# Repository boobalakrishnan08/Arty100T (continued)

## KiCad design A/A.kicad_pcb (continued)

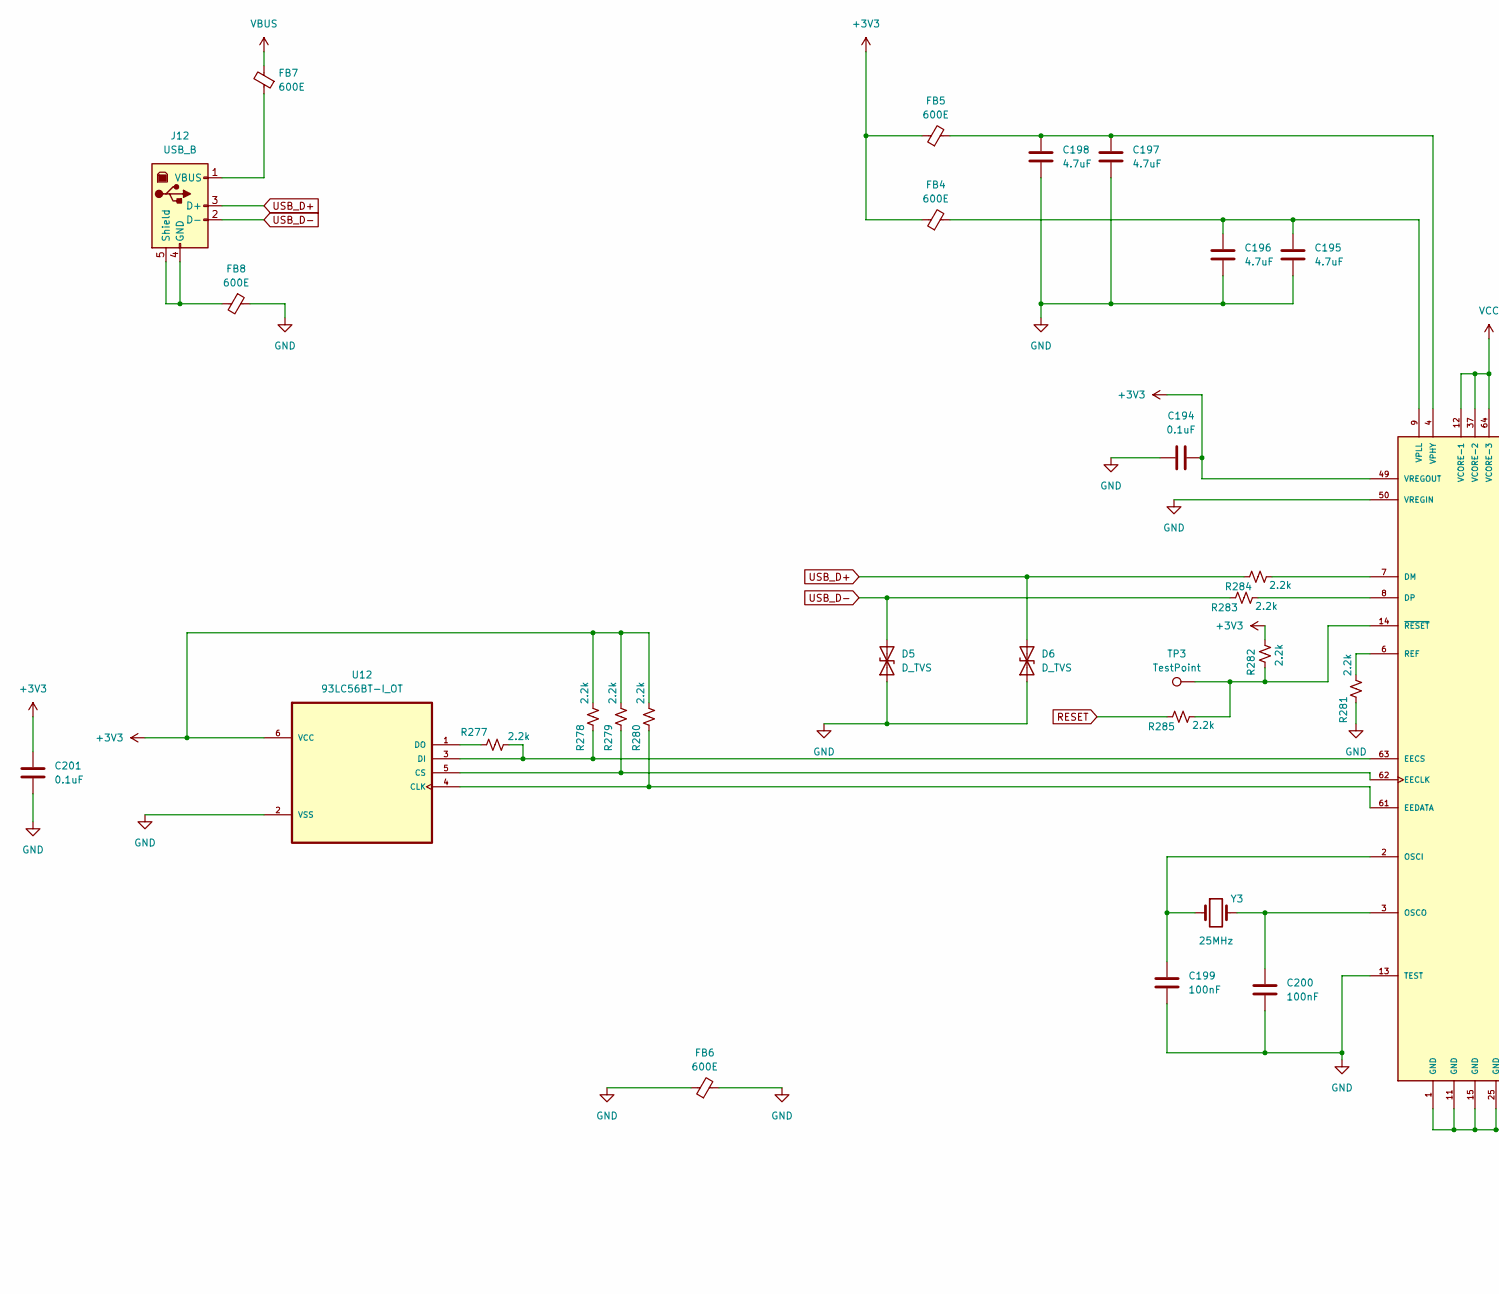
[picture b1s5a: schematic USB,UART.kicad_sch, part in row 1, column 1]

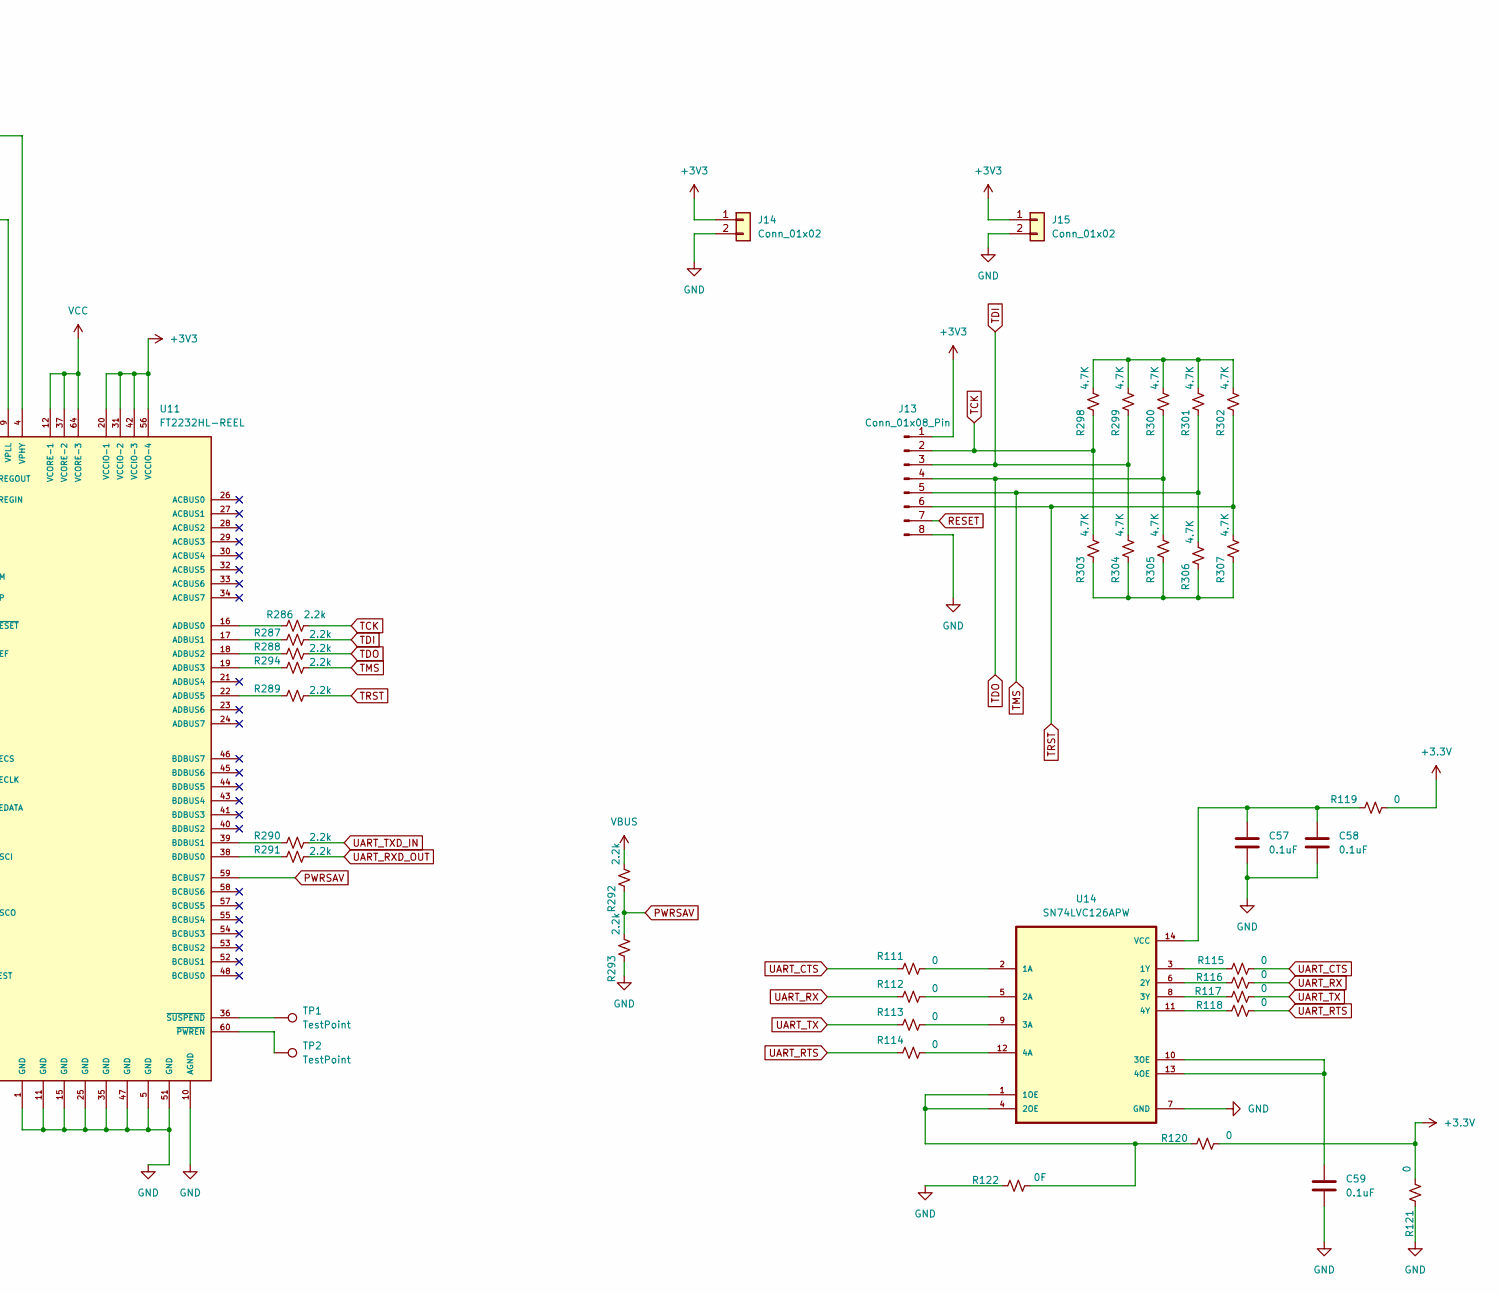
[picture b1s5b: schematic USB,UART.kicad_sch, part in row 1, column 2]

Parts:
C57, C58, C59, C194, C201: 0.1uF; C_0402_1005Metric
C195, C196, C197, C198: 4.7uF; C_0402_1005Metric
C199, C200: 100nF; C_0402_1005Metric
D5, D6: D_TVS; D_0603_1608Metric
FB4, FB5, FB6, FB7, FB8: 600E; L_0402_1005Metric
J12: USB_B; USB_Micro-B_Amphenol_10103594-0001LF_Horizontal
J13: Conn_01x08_Pin; PinHeader_1x08_P2.54mm_Vertical
J14, J15: Conn_01x02; PinHeader_1x02_P2.54mm_Vertical
R111, R112, R113, R114, R115, R116, R117, R118, R119, R120, R121: 0; R_0402_1005Metric
R122: 0F; R_0402_1005Metric
R277, R278, R279, R280, R281, R282, R283, R284, R285, R286, R287, R288, R289, R290, R291, R292, R293, R294: 2.2k; R_0402_1005Metric
R298, R299, R300, R301, R302, R303, R304, R305, R306, R307: 4.7K; R_0402_1005Metric
TP1, TP2, TP3: TestPoint; TestPoint_Bridge_Pitch2.54mm_Drill0.7mm
U11: FT2232HL-REEL; QFP50P1200X1200X160-64N
U12: 93LC56BT-I_OT; SOT95P280X145-6N
U14: SN74LVC126APW; SOP65P640X120-14N
Y3: 25MHz; Crystal_SMD_SeikoEpson_FA128-4Pin_2.0x1.6mm

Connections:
+3.3V: R119.2, R120.2, R121.2; also elsewhere on the board
+3V3: C194.2, C201.1, FB4.1, FB5.1, J13.1, J14.1, J15.1, R278.2, R279.2, R280.2, R282.2, U11.20 (VCCIO-1), U11.31 (VCCIO-2), U11.42 (VCCIO-3), U11.49 (VREGOUT), U11.56 (VCCIO-4), U12.6 (VCC); also elsewhere on the board
GND: C57.2, C58.2, C59.2, C194.1, C195.2, C196.2, C197.2, C198.2, C199.2, C200.2, C201.2, D5.1 (A1), D6.1 (A1), FB6.1, FB6.2, FB8.1, J13.8, J14.2, J15.2, R121.1, R122.1, R281.1, R293.1, U11.1 (GND), U11.5 (GND), U11.10 (AGND), U11.11 (GND), U11.13 (TEST), U11.15 (GND), U11.25 (GND), U11.35 (GND), U11.47 (GND), U11.50 (VREGIN), U11.51 (GND), U12.2 (VSS), U14.7 (GND); also elsewhere on the board
unnamed: FB8.2, J12.4 (GND), J12.5 (Shield)
unnamed: FB7.1, J12.1 (VBUS)
unnamed: R298.2, R299.2, R300.2, R301.2, R302.2
unnamed: R303.1, R304.1, R305.1, R306.1, R307.1
unnamed: R286.1, U11.16 (ADBUS0)
unnamed: R287.1, U11.17 (ADBUS1)
unnamed: R288.1, U11.18 (ADBUS2)
unnamed: R294.1, U11.19 (ADBUS3)
unnamed: R289.1, U11.22 (ADBUS5)
unnamed: R291.1, U11.38 (BDBUS0)
unnamed: R290.1, U11.39 (BDBUS1)
unnamed: R284.2, U11.7 (DM)
unnamed: R283.2, U11.8 (DP)
unnamed: R279.1, U11.62 (EECLK), U12.5 (CS)
unnamed: R277.2, R278.1, U11.63 (EECS), U12.3 (DI)
unnamed: R280.1, U11.61 (EEDATA), U12.4 (CLK)
unnamed: C199.1, U11.2 (OSCI), Y3.1
unnamed: C200.1, U11.3 (OSCO), Y3.2
unnamed: R281.2, U11.6 (REF)
unnamed: C197.1, C198.1, FB5.2, U11.4 (VPHY)
unnamed: C195.1, C196.1, FB4.2, U11.9 (VPLL)
unnamed: TP2.1, U11.60 (~PWREN)
unnamed: R282.1, R285.2, TP3.1, U11.14 (~RESET)
unnamed: TP1.1, U11.36 (~SUSPEND)
unnamed: R277.1, U12.1 (DO)
unnamed: R111.2, U14.2 (1A)
unnamed: R120.1, R122.2, U14.1 (1OE), U14.4 (2OE)
unnamed: R115.1, U14.3 (1Y)
unnamed: R112.2, U14.5 (2A)
unnamed: R116.1, U14.6 (2Y)
unnamed: R113.2, U14.9 (3A)
unnamed: C59.1, U14.10 (3OE), U14.13 (4OE)
unnamed: R117.1, U14.8 (3Y)
unnamed: R114.2, U14.12 (4A)
unnamed: R118.1, U14.11 (4Y)
unnamed: C57.1, C58.1, R119.1, U14.14 (VCC)
PWRSAV: R292.1, R293.2, U11.59 (BCBUS7)
RESET: J13.7, R285.1
TCK: J13.2, R286.2, R298.1, R303.2; also elsewhere on the board
TDI: J13.3, R287.2, R299.1, R304.2
TDO: J13.4, R288.2, R300.1, R305.2
TMS: J13.5, R294.2, R301.1, R306.2; also elsewhere on the board
TRST: J13.6, R289.2, R302.1, R307.2
UART_CTS: R111.1, R115.2
UART_RTS: R114.1, R118.2
UART_RX: R112.1, R116.2
UART_RXD_OUT: R291.2; also elsewhere on the board
UART_TX: R113.1, R117.2
UART_TXD_IN: R290.2; also elsewhere on the board
USB_D+: D6.2 (A2), J12.3 (D+), R284.1
USB_D-: D5.2 (A2), J12.2 (D-), R283.1
VBUS: FB7.2, R292.2; also elsewhere on the board
VCC: U11.12 (VCORE-1), U11.37 (VCORE-2), U11.64 (VCORE-3)

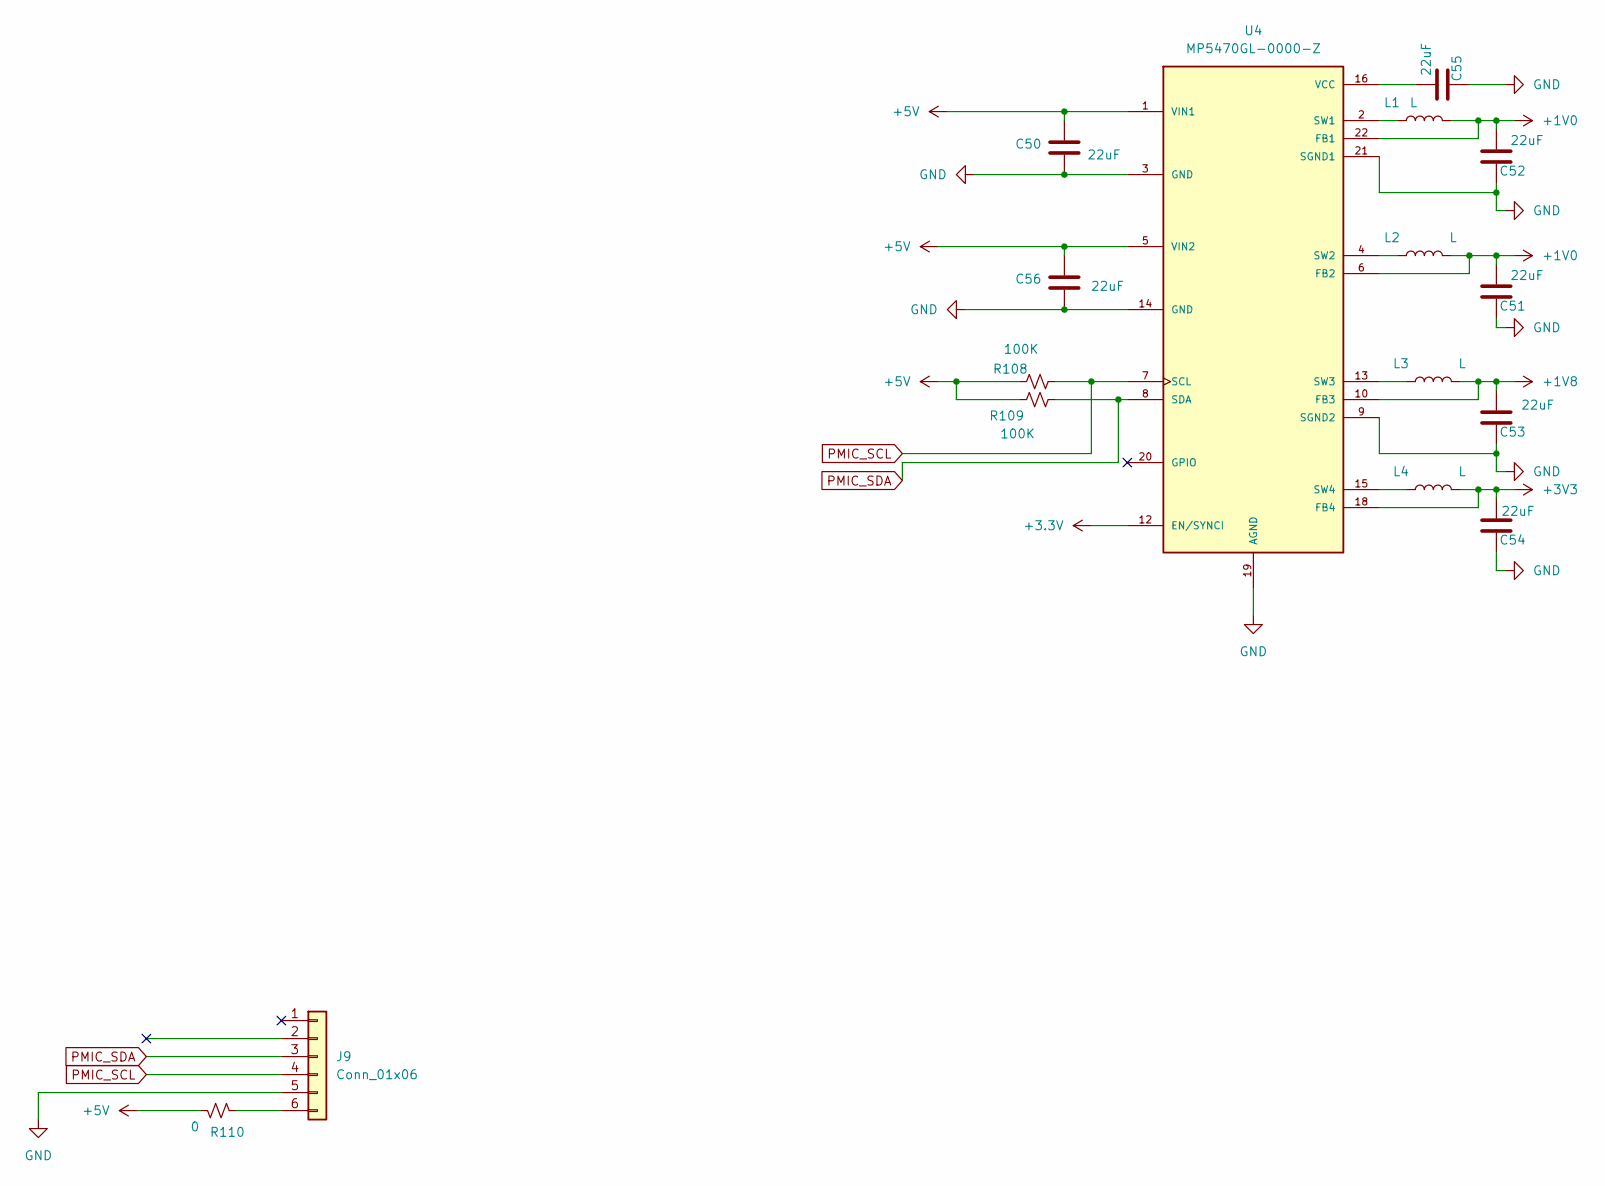
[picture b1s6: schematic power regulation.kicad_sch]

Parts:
C50, C51, C52, C53, C54, C55, C56: 22uF; C_0402_1005Metric
J9: Conn_01x06; PinSocket_1x06_P2.54mm_Vertical
L1, L2, L3, L4: L; L_0201_0603Metric
R108, R109: 100K; R_0402_1005Metric
R110: 0; R_0402_1005Metric
U4: MP5470GL-0000-Z; IC_MP5470GL-0000-Z; PARTREV 1.0

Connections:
+1V0: C51.1, C52.1, L1.2, L2.2, U4.6 (FB2), U4.22 (FB1); also elsewhere on the board
+1V8: C53.1, L3.2, U4.10 (FB3); also elsewhere on the board
+3.3V: U4.12 (EN/SYNCI); also elsewhere on the board
+3V3: C54.1, L4.2, U4.18 (FB4); also elsewhere on the board
+5V: C50.1, C56.1, R108.1, R109.1, R110.1, U4.1 (VIN1), U4.5 (VIN2); also elsewhere on the board
GND: C50.2, C51.2, C52.2, C53.2, C54.2, C55.2, C56.2, J9.5, U4.3 (GND), U4.9 (SGND2), U4.14 (GND), U4.19 (AGND), U4.21 (SGND1); also elsewhere on the board
unnamed: J9.6, R110.2
unnamed: L1.1, U4.2 (SW1)
unnamed: L2.1, U4.4 (SW2)
unnamed: L3.1, U4.13 (SW3)
unnamed: L4.1, U4.15 (SW4)
unnamed: C55.1, U4.16 (VCC)
PMIC_SCL: J9.4, R108.2, U4.7 (SCL)
PMIC_SDA: J9.3, R109.2, U4.8 (SDA)

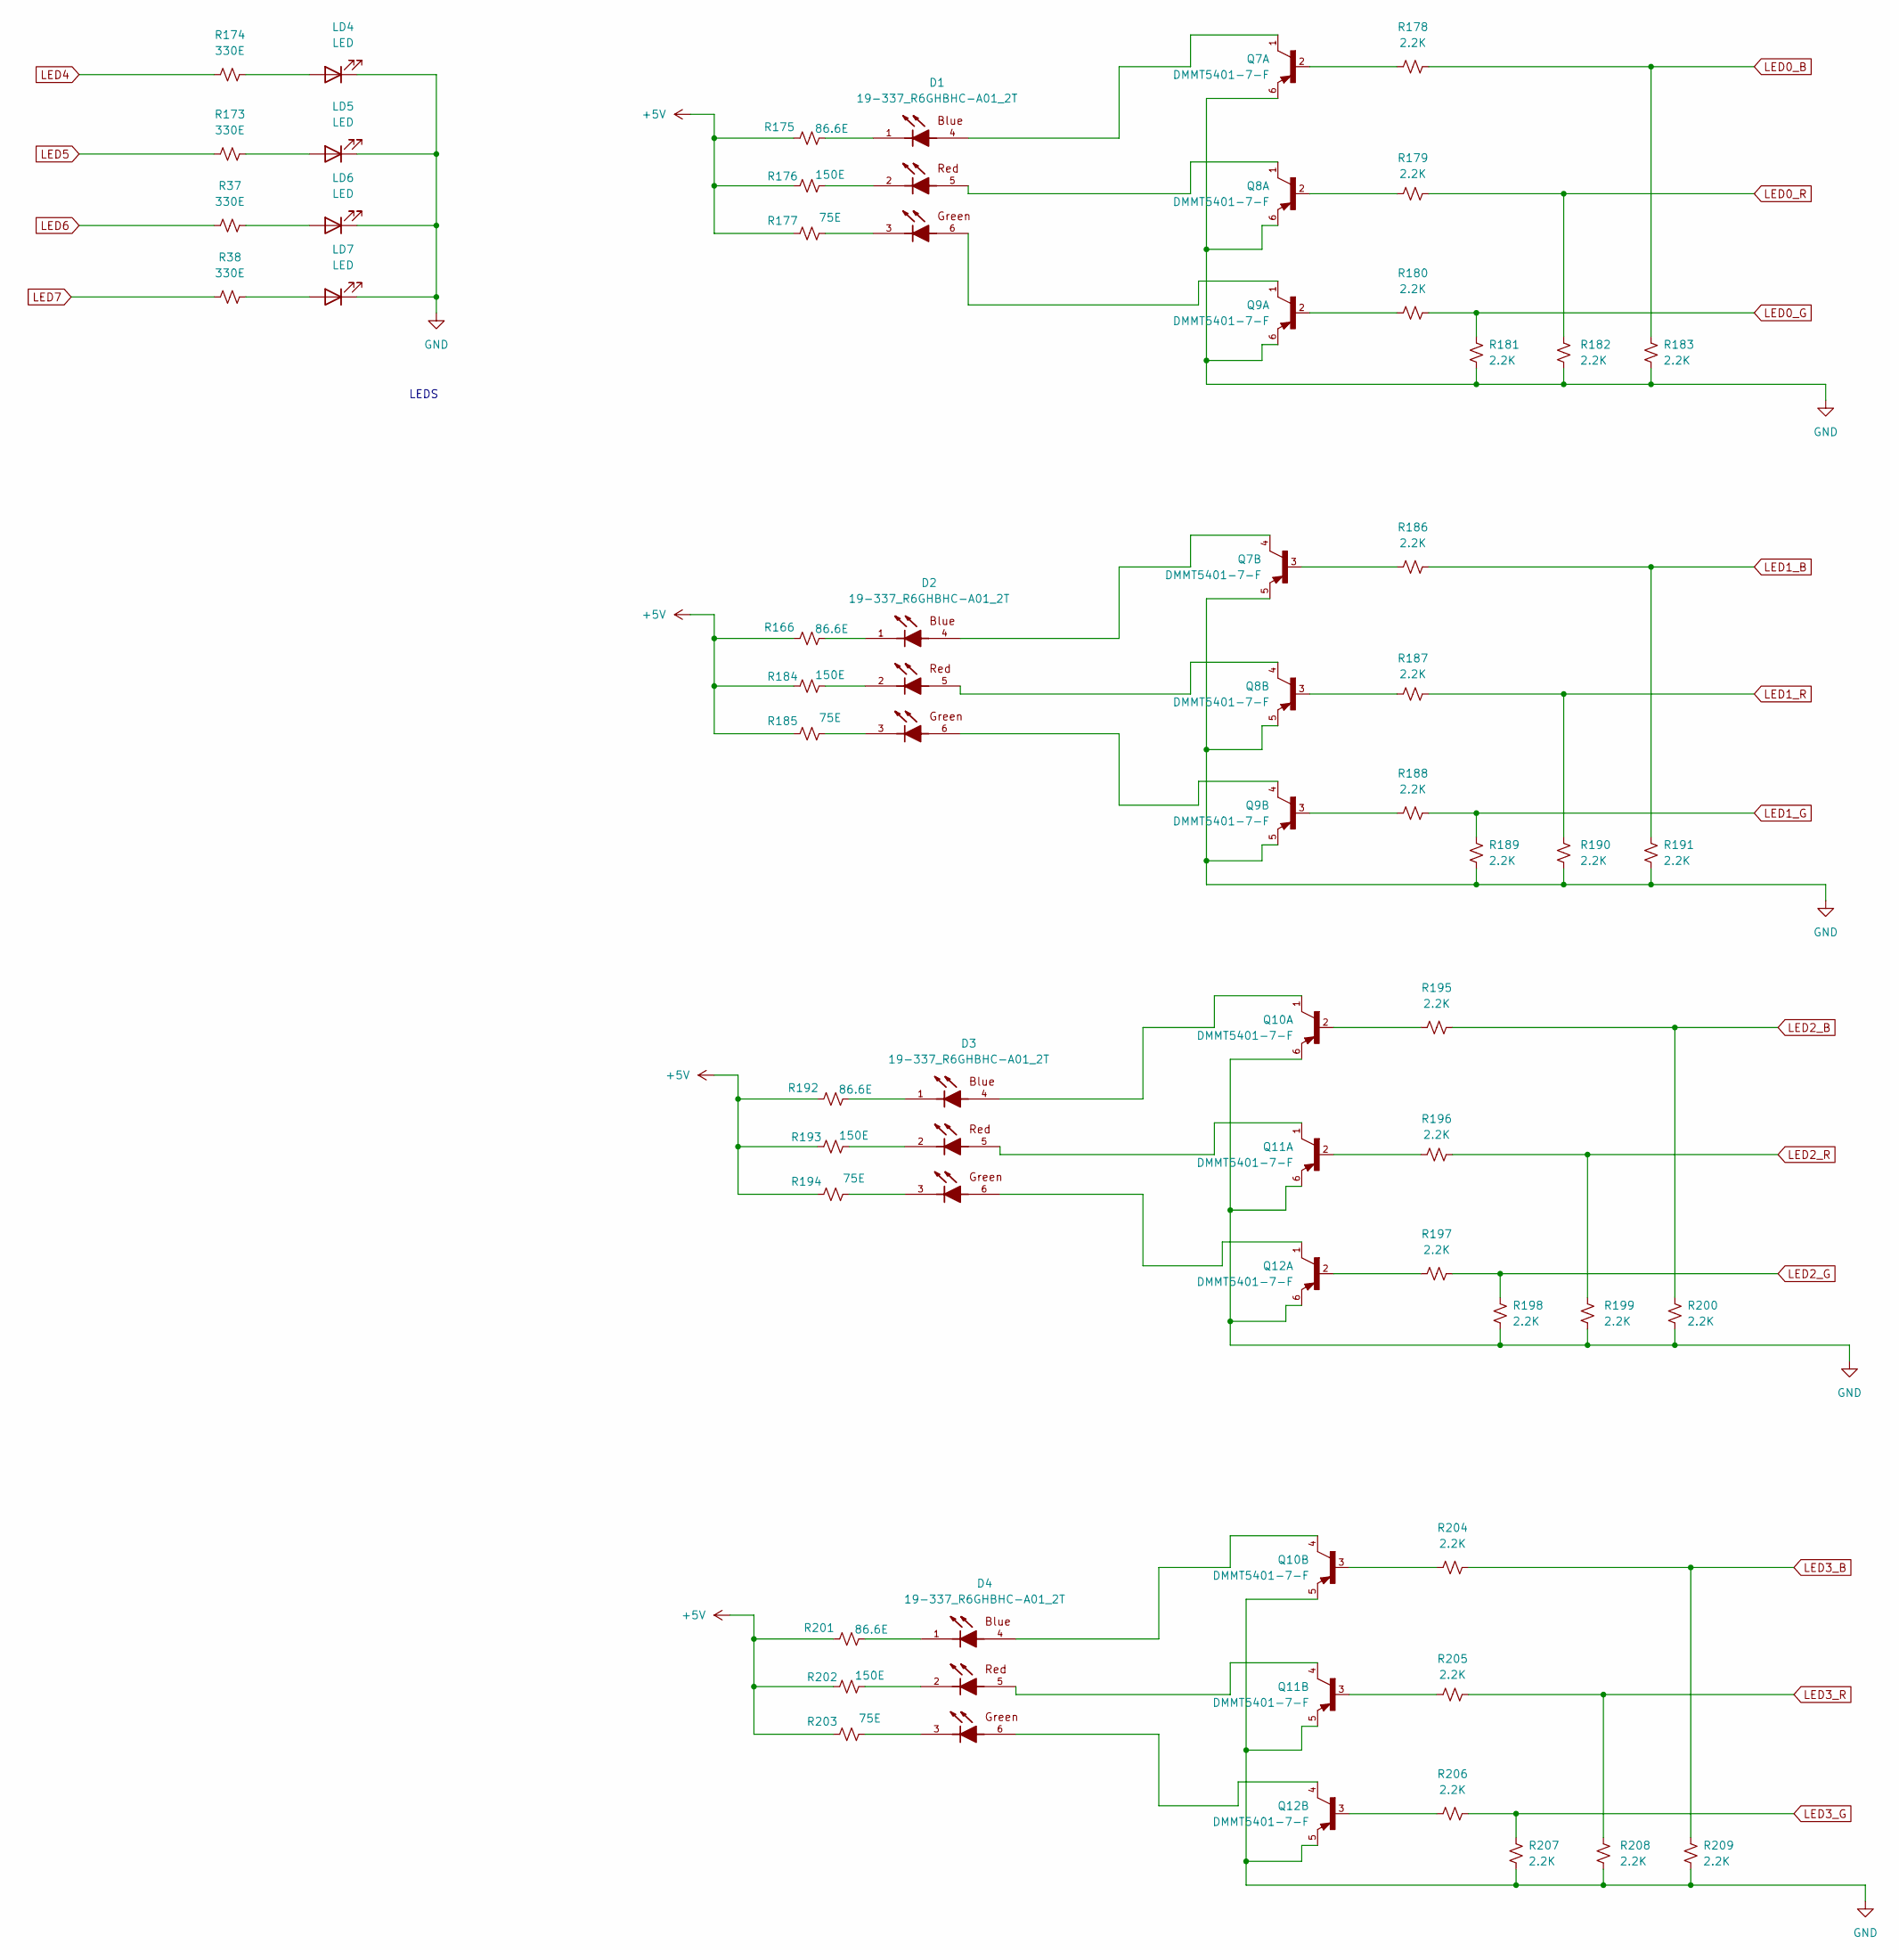
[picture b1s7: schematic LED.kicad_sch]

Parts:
D1, D2, D3, D4: 19-337_R6GHBHC-A01_2T; LED_19-337_R6GHBHC-A01_2T
LD4, LD5, LD6, LD7: LED; LED_01005_0402Metric
Q7, Q8, Q9, Q10, Q11, Q12: DMMT5401-7-F; SOT95P285X140-6N; PARTREV 8
R37, R38, R173, R174: 330E; R_0402_1005Metric
R166, R175, R192, R201: 86.6E; R_0402_1005Metric
R176, R184, R193, R202: 150E; R_0402_1005Metric
R177, R185, R194, R203: 75E; R_0402_1005Metric
R178, R179, R180, R181, R182, R183, R186, R187, R188, R189, R190, R191, R195, R196, R197, R198, R199, R200, R204, R205, R206, R207, R208, R209: 2.2K; R_0402_1005Metric

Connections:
+5V: R166.1, R175.1, R176.1, R177.1, R184.1, R185.1, R192.1, R193.1, R194.1, R201.1, R202.1, R203.1; also elsewhere on the board
GND: LD4.1 (K), LD5.1 (K), LD6.1 (K), LD7.1 (K), Q7.5, Q7.6, Q8.5, Q8.6, Q9.5, Q9.6, Q10.5, Q10.6, Q11.5, Q11.6, Q12.5, Q12.6, R181.1, R182.1, R183.1, R189.1, R190.1, R191.1, R198.1, R199.1, R200.1, R207.1, R208.1, R209.1; also elsewhere on the board
LED0_B: R178.2, R183.2; also elsewhere on the board
LED0_G: R180.2, R181.2; also elsewhere on the board
LED0_R: R179.2, R182.2; also elsewhere on the board
LED1_B: R186.2, R191.2; also elsewhere on the board
LED1_G: R188.2, R189.2; also elsewhere on the board
LED1_R: R187.2, R190.2; also elsewhere on the board
LED2_B: R195.2, R200.2; also elsewhere on the board
LED2_G: R197.2, R198.2; also elsewhere on the board
LED2_R: R196.2, R199.2; also elsewhere on the board
LED3_B: R204.2, R209.2; also elsewhere on the board
LED3_G: R206.2, R207.2
LED3_R: R205.2, R208.2; also elsewhere on the board
LED4: R174.1; also elsewhere on the board
LED5: R173.1; also elsewhere on the board
LED6: R37.1; also elsewhere on the board
LED7: R38.1; also elsewhere on the board
unnamed: D1.1, R175.2
unnamed: D1.2, R176.2
unnamed: D1.3, R177.2
unnamed: D1.4, Q7.1
unnamed: D1.5, Q8.1
unnamed: D1.6, Q9.1
unnamed: D2.1, R166.2
unnamed: D2.2, R184.2
unnamed: D2.3, R185.2
unnamed: D2.4, Q7.4
unnamed: D2.5, Q8.4
unnamed: D2.6, Q9.4
unnamed: D3.1, R192.2
unnamed: D3.2, R193.2
unnamed: D3.3, R194.2
unnamed: D3.4, Q10.1
unnamed: D3.5, Q11.1
unnamed: D3.6, Q12.1
unnamed: D4.1, R201.2
unnamed: D4.2, R202.2
unnamed: D4.3, R203.2
unnamed: D4.4, Q10.4
unnamed: D4.5, Q11.4
unnamed: D4.6, Q12.4
unnamed: LD4.2 (A), R174.2
unnamed: LD5.2 (A), R173.2
unnamed: LD6.2 (A), R37.2
unnamed: LD7.2 (A), R38.2
unnamed: Q7.2, R178.1
unnamed: Q7.3, R186.1
unnamed: Q8.2, R179.1
unnamed: Q8.3, R187.1
unnamed: Q9.2, R180.1
unnamed: Q9.3, R188.1
unnamed: Q10.2, R195.1
unnamed: Q10.3, R204.1
unnamed: Q11.2, R196.1
unnamed: Q11.3, R205.1
unnamed: Q12.2, R197.1
unnamed: Q12.3, R206.1

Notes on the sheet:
LEDS

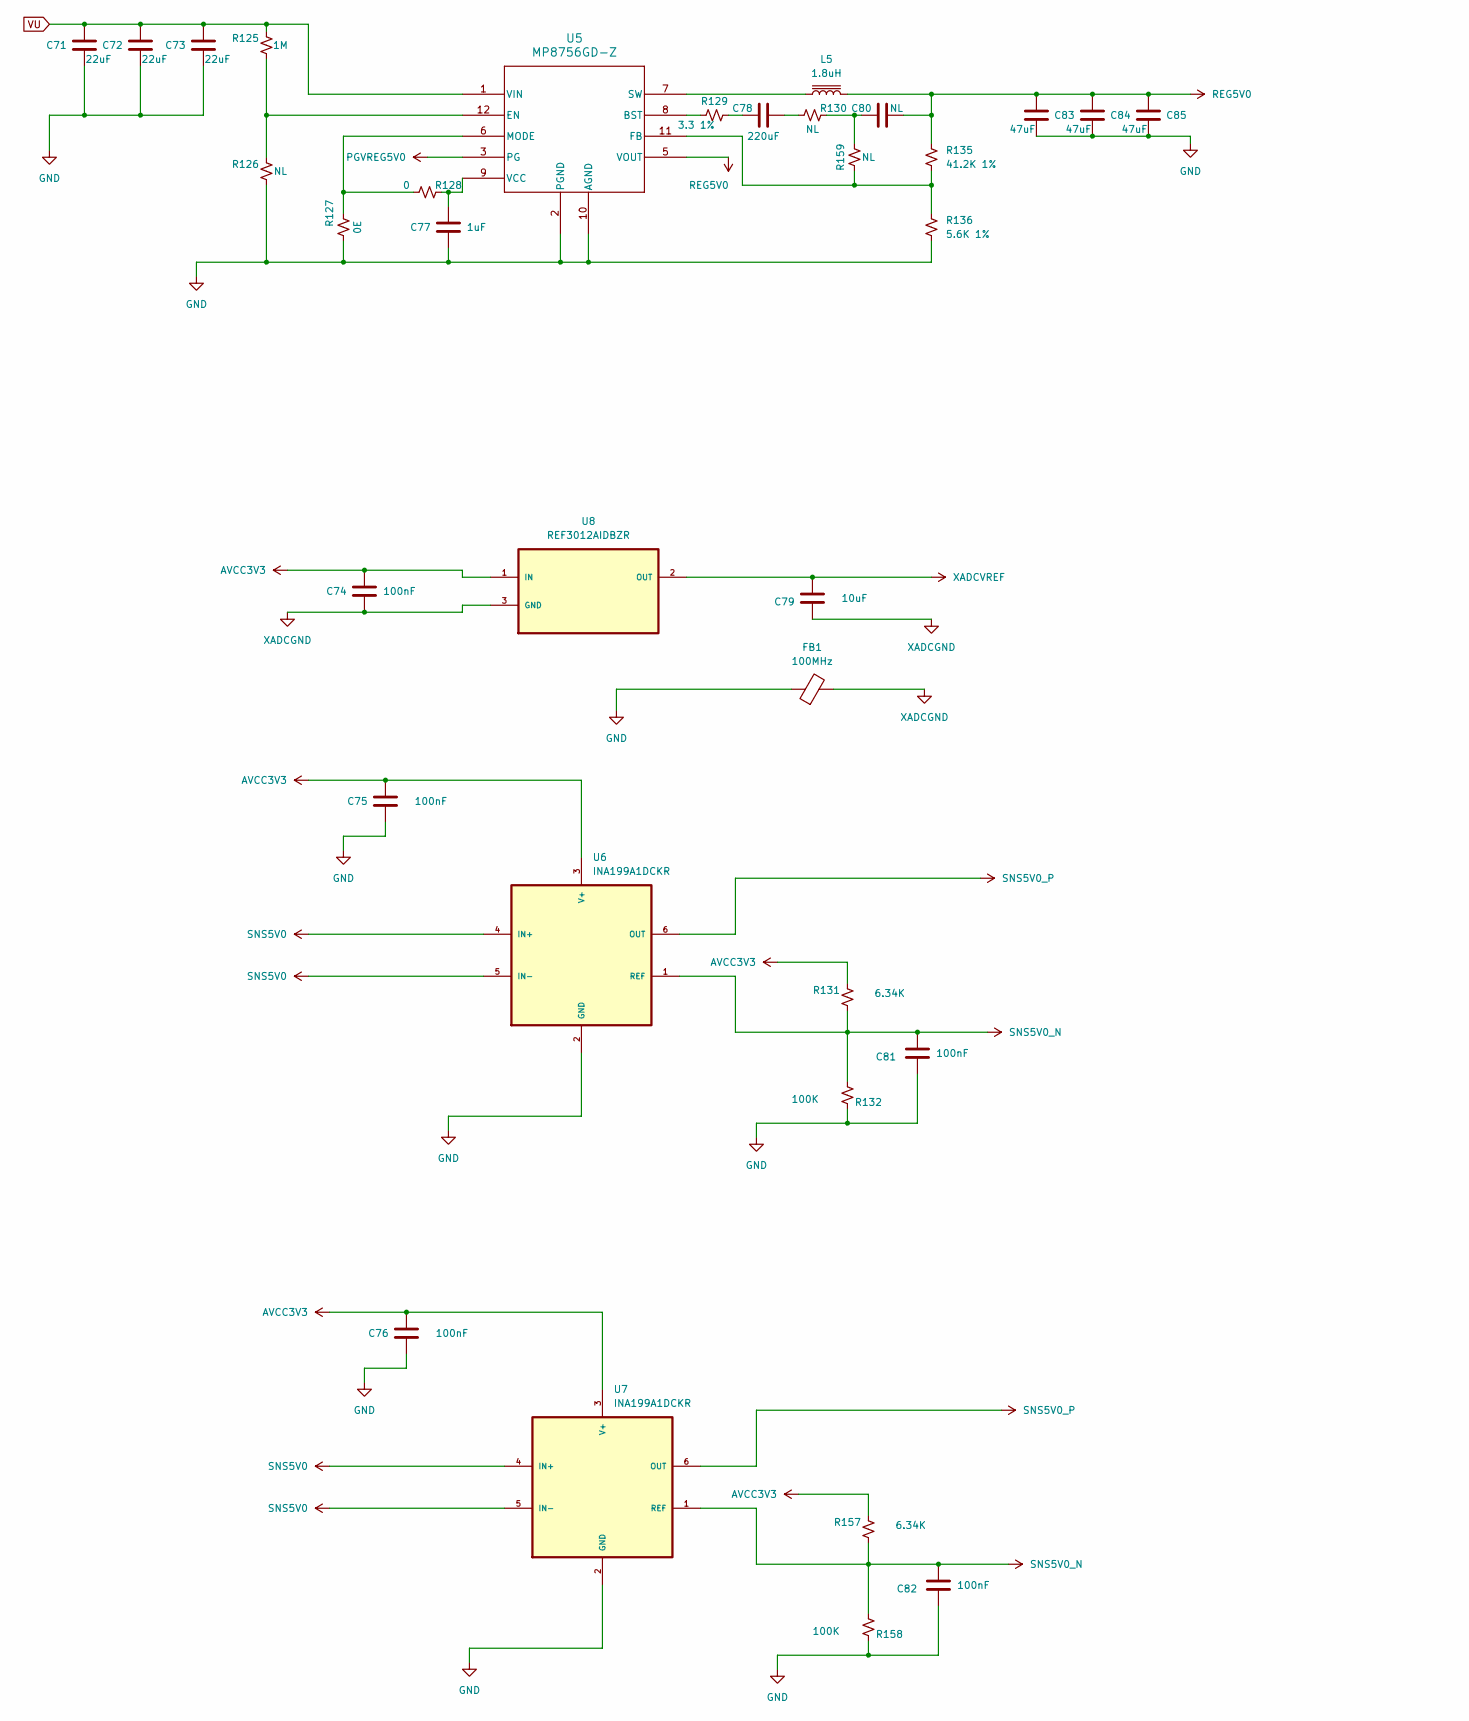
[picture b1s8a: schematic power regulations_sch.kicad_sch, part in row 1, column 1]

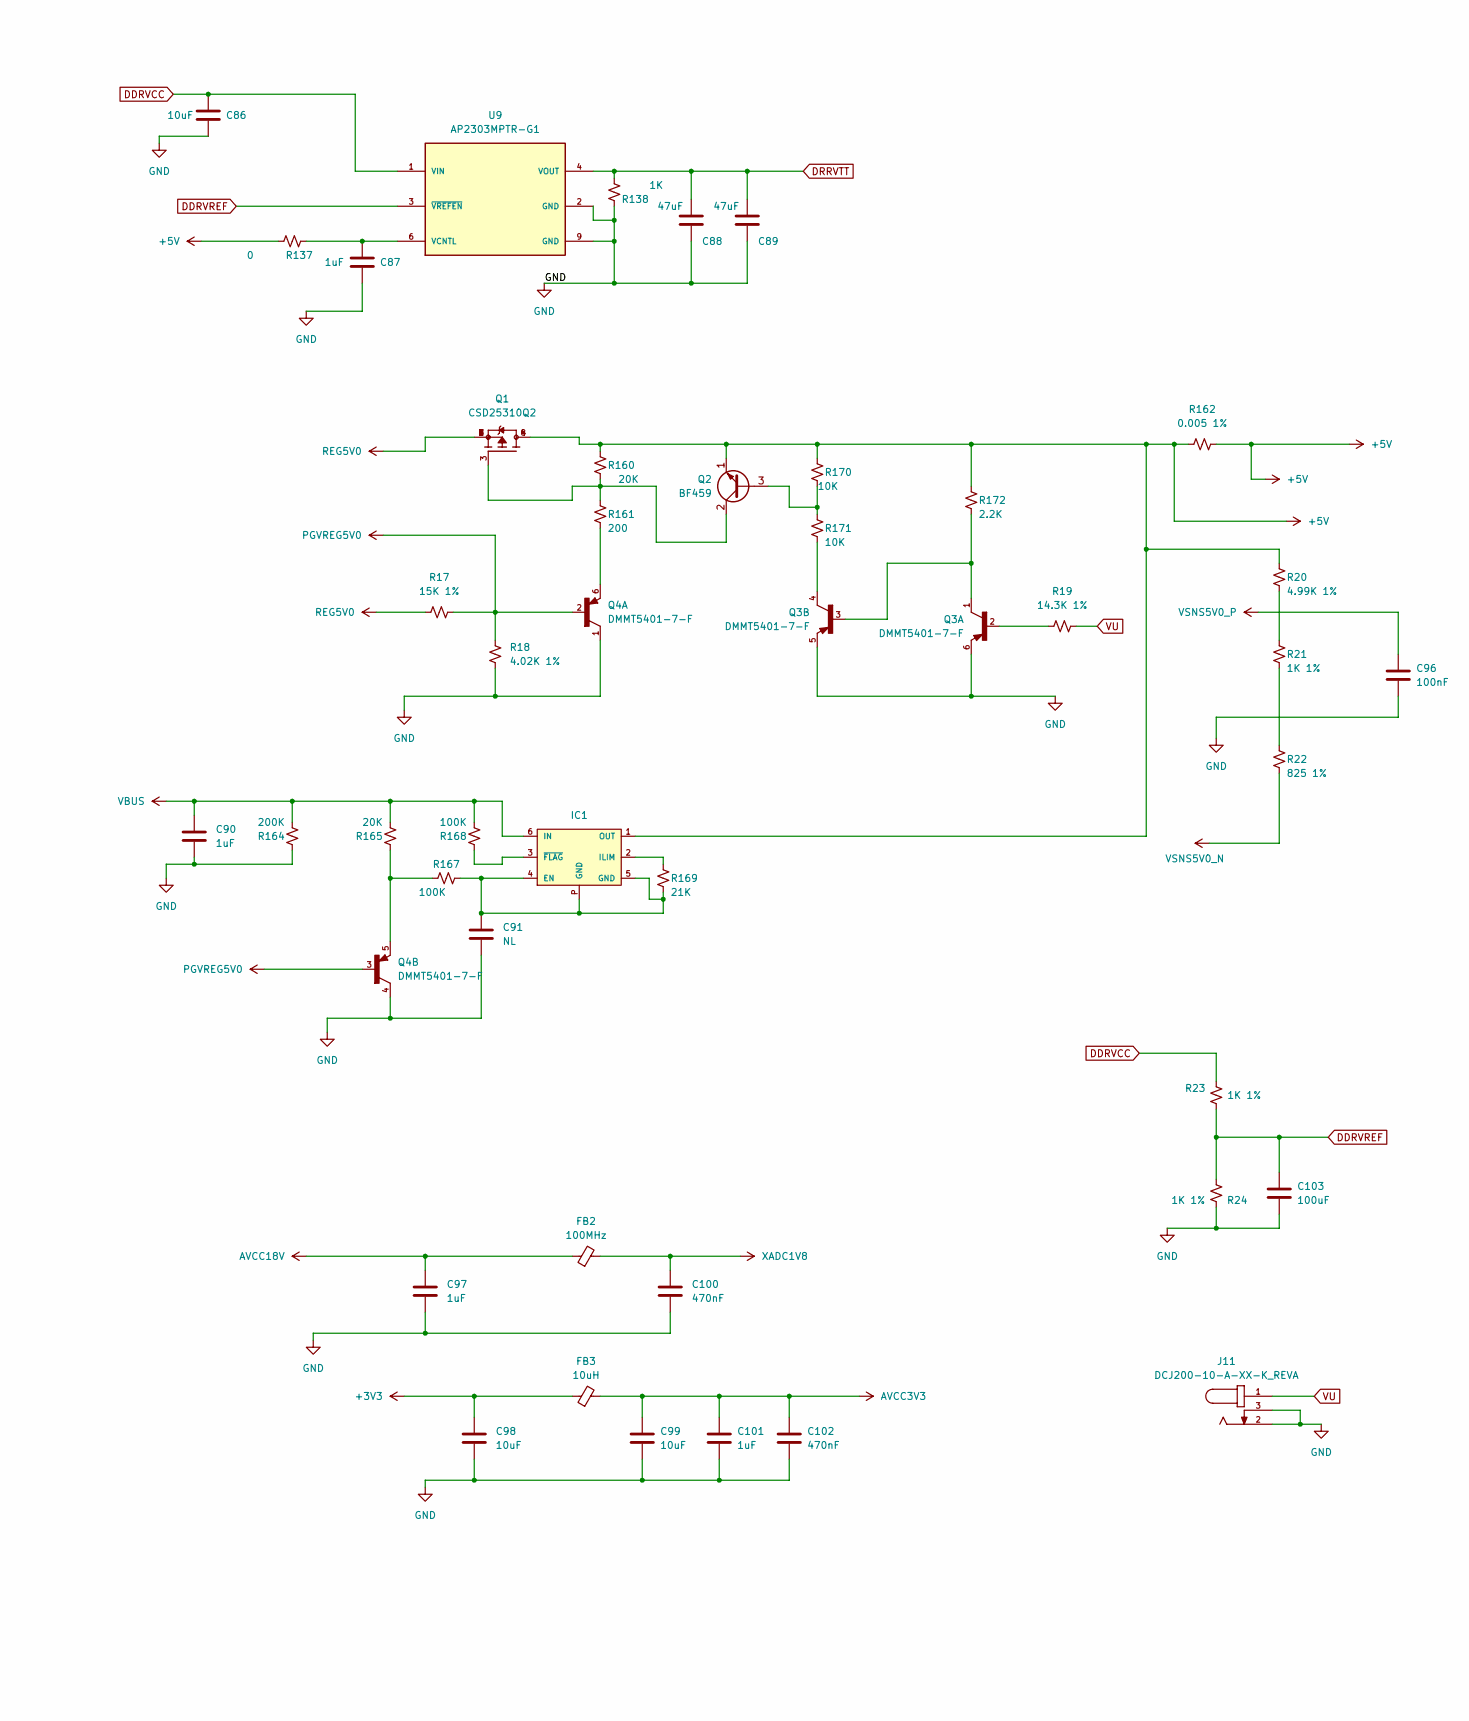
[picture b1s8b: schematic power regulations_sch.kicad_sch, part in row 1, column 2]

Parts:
C71, C72, C73: 22uF; C_0805_2012Metric
C74, C96: 100nF; C_0201_0603Metric
C75, C76, C81, C82: 100nF; C_1206_3216Metric
C77, C87, C90, C97, C101: 1uF; C_0805_2012Metric
C78: 220uF; C_1206_3216Metric
C79, C86, C98, C99: 10uF; C_1206_3216Metric
C80, C91: NL; C_0402_1005Metric
C83, C84, C85, C88, C89: 47uF; C_0402_1005Metric
C100, C102: 470nF; C_0603_1608Metric
C103: 100uF; C_1206_3216Metric
FB1, FB2: 100MHz; L_0402_1005Metric
FB3: 10uH; L_0402_1005Metric
IC1: NCP380 ADJ; TRANS_NTLUS3A18PZTAG; MPN NCP380HMUAJAATBG
J11: DCJ200-10-A-XX-K_REVA; GCT_DCJ200-10-A-XX-K_REVA; PARTREV A
L5: 1.8uH; L_0402_1005Metric
Q1: CSD25310Q2; TRANS_CSD25310Q2
Q2: BF459; TO-126-3_Vertical
Q3, Q4: DMMT5401-7-F; SOT95P285X140-6N; PARTREV 8
R17: 15K 1%; R_0402_1005Metric
R18: 4.02K 1%; R_0402_1005Metric
R19: 14.3K 1%; R_0402_1005Metric
R20: 4.99K 1%; R_0402_1005Metric
R21, R23, R24: 1K 1%; R_0402_1005Metric
R22: 825 1%; R_0402_1005Metric
R125: 1M; R_0402_1005Metric
R126, R130, R159: NL; C_0402_1005Metric
R127: 0E; R_0402_1005Metric
R128, R137: 0; R_0402_1005Metric
R129: 3.3 1%; R_0402_1005Metric
R131, R157: 6.34K; R_0402_1005Metric
R132, R158, R167, R168: 100K; R_0402_1005Metric
R135: 41.2K 1%; R_0402_1005Metric
R136: 5.6K 1%; R_0402_1005Metric
R138: 1K; R_0402_1005Metric
R160, R165: 20K; R_0402_1005Metric
R161: 200; R_0402_1005Metric
R162: 0.005 1%; R_0402_1005Metric
R164: 200K; R_0402_1005Metric
R169: 21K; R_0402_1005Metric
R170, R171: 10K; R_0402_1005Metric
R172: 2.2K; R_0402_1005Metric
U5: MP8756GD-Z; QFN-12_MP8756_MNP
U6, U7: INA199A1DCKR; SOT65P210X110-6N
U8: REF3012AIDBZR; SOT95P237X112-3N; MPN REF3120AIDBZT
U9: AP2303MPTR-G1; SOIC127P600X155-9N; PARTREV 3 - 2

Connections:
+3V3: C98.1, FB3.1; also elsewhere on the board
+5V: IC1.1 (OUT), Q1.4, Q1.8, Q2.1 (E), R20.2, R137.1, R160.2, R162.1, R162.2, R170.2, R172.2; also elsewhere on the board
AVCC3V3: C74.2, C75.2, C76.2, C99.1, C101.1, C102.1, FB3.2, R131.2, R157.2, U6.3 (V+), U7.3 (V+), U8.1 (IN)
AVCC18V: C97.1, FB2.1
DDRVCC: C86.1, R23.2, U9.1 (VIN); also elsewhere on the board
DDRVREF: C103.1, R23.1, R24.1, U9.3 (~VREFEN)
DRRVTT: C88.1, C89.1, R138.1, U9.4 (VOUT)
GND: C71.1, C72.1, C73.1, C75.1, C76.1, C77.1, C81.1, C82.1, C83.2, C84.2, C85.2, C86.2, C87.2, C88.2, C89.2, C90.2, C91.2, C96.2, C97.2, C98.2, C99.2, C100.2, C101.2, C102.2, C103.2, FB1.1, J11.2, J11.3, Q3.5, Q3.6, Q4.1, Q4.4, R18.1, R24.2, R126.1, R127.1, R132.2, R136.2, R138.2, R158.2, R164.2, U5.2 (PGND), U5.10 (AGND), U6.2 (GND), U7.2 (GND), U9.2 (GND), U9.9 (GND); also elsewhere on the board
unnamed: C78.1, R129.2
unnamed: C78.2, R130.1
unnamed: C80.1, R130.2, R159.2
unnamed: C91.1, IC1.4 (EN), IC1.5 (GND), IC1.P (GND), R167.2, R169.1
unnamed: IC1.2 (ILIM), R169.2
unnamed: IC1.3 (~FLAG), R168.2
unnamed: Q2.3 (B), R170.1, R171.2
unnamed: Q1.3, Q2.2 (C), R160.1, R161.2
unnamed: Q3.1, Q3.3, R172.1
unnamed: Q3.2, R19.1
unnamed: Q3.4, R171.1
unnamed: Q4.5, R165.2, R167.1
unnamed: Q4.6, R161.1
unnamed: R20.1, R21.2
unnamed: R21.1, R22.2
unnamed: R129.1, U5.8 (BST)
unnamed: R125.1, R126.2, U5.12 (EN)
unnamed: R135.2, R136.1, R159.1, U5.11 (FB)
unnamed: R127.2, R128.1, U5.6 (MODE)
unnamed: L5.1, U5.7 (SW)
unnamed: C77.2, R128.2, U5.9 (VCC)
unnamed: C87.1, R137.2, U9.6 (VCNTL)
PGVREG5V0: Q4.2, Q4.3, R17.2, R18.2, U5.3 (PG)
REG5V0: C80.2, C83.1, C84.1, C85.1, L5.2, Q1.1, Q1.2, Q1.5, Q1.6, Q1.7, R17.1, R135.1, U5.5 (VOUT)
SNS5V0: U6.4 (IN+), U6.5 (IN-), U7.4 (IN+), U7.5 (IN-)
SNS5V0_N: C81.2, C82.2, R131.1, R132.1, R157.1, R158.1, U6.1 (REF), U7.1 (REF); also elsewhere on the board
SNS5V0_P: U6.6 (OUT), U7.6 (OUT); also elsewhere on the board
VBUS: C90.1, IC1.6 (IN), R164.1, R165.1, R168.1; also elsewhere on the board
VSNS5V0_N: R22.1; also elsewhere on the board
VSNS5V0_P: C96.1; also elsewhere on the board
VU: C71.2, C72.2, C73.2, J11.1, R19.2, R125.2, U5.1 (VIN); also elsewhere on the board
XADC1V8: C100.1, FB2.2; also elsewhere on the board
XADCGND: C74.1, C79.1, FB1.2, U8.3 (GND); also elsewhere on the board
XADCVREF: C79.2, U8.2 (OUT); also elsewhere on the board

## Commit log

2025-06-17 Add files via upload
    Updated
